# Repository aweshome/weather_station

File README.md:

# Weather station

## Internal unit (terminal)

### Heart:
	ATmega1284
	
### Peripherals:
	EG9018C - 640x480 8.4" mono lcd screen
	DS3231 - rtc
	BMP180 - pressure sensor
	nRF24L01 - wireless transceiver
	AM2302 - temperature and humidity sensor

## External unit (sensor)

### Heart:
	ATxmega128A3U - uC
	
### Peripherals:
	PMSA003 - dust sensor
	nRF24L01
	AM2302

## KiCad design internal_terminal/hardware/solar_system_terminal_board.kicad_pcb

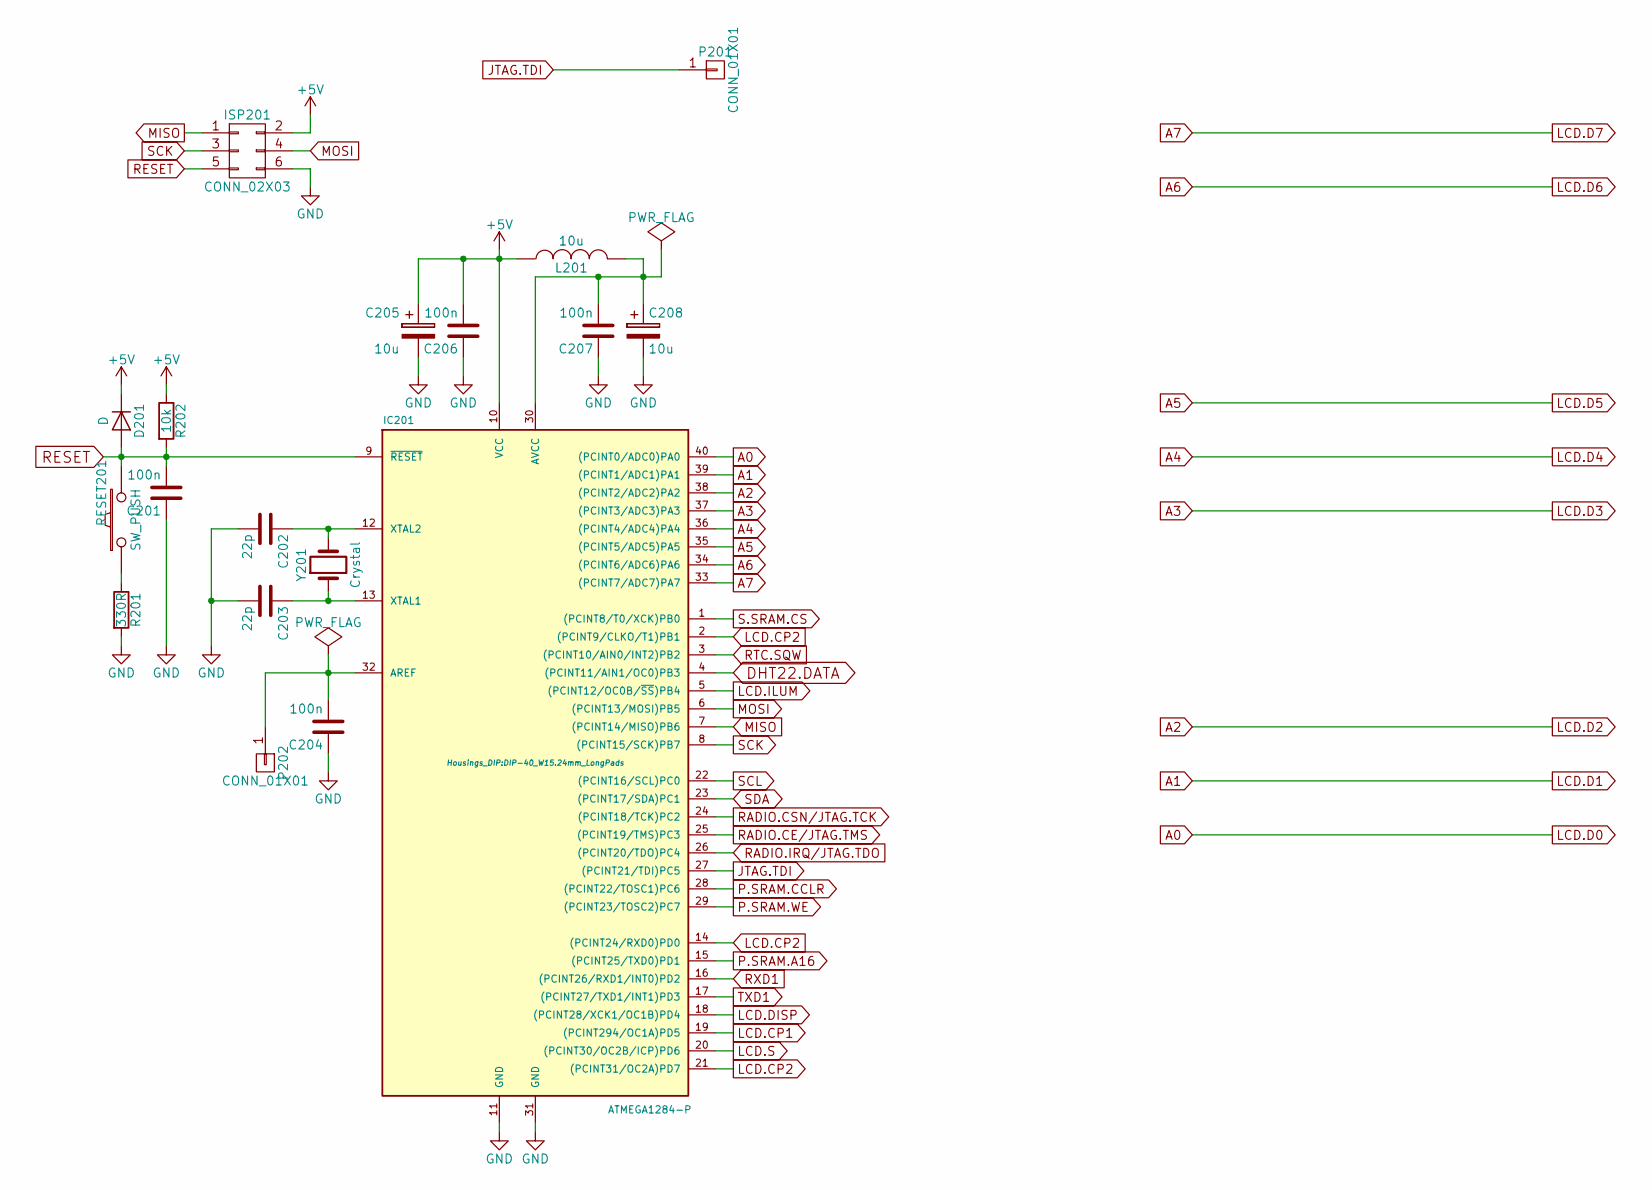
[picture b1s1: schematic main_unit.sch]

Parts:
C201, C204, C206, C207: 100n; C_1206_HandSoldering
C202, C203: 22p; C_1206_HandSoldering
C205, C208: 10u; TantalC_SizeB_EIA-3528_HandSoldering
D201: D; Diode-MiniMELF_Handsoldering
IC201: ATMEGA1284-P; DIP-40_W15.24mm_LongPads
ISP201: CONN_02X03; Pin_Header_Angled_2x03
L201: 10u; Neosid_Inductor_SM-NE45_SMD1812
P201, P202: CONN_01X01; Pin_Header_Straight_1x01
R201: 330R; R_1206_HandSoldering
R202: 10k; R_1206_HandSoldering
RESET201: SW_PUSH; SW_Tactile_SPST_Angled
Y201: Crystal; Crystal_HC49-U_Horizontal_Typ1

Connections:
+5V: C205.1, C206.2, D201.1 (K), IC201.10 (VCC), ISP201.2, L201.1, R202.1; also elsewhere on the board
A0: IC201.40 ((PCINT0/ADC0)PA0); also elsewhere on the board
A1: IC201.39 ((PCINT1/ADC1)PA1); also elsewhere on the board
A2: IC201.38 ((PCINT2/ADC2)PA2); also elsewhere on the board
A3: IC201.37 ((PCINT3/ADC3)PA3); also elsewhere on the board
A4: IC201.36 ((PCINT4/ADC4)PA4); also elsewhere on the board
A5: IC201.35 ((PCINT5/ADC5)PA5); also elsewhere on the board
A6: IC201.34 ((PCINT6/ADC6)PA6); also elsewhere on the board
A7: IC201.33 ((PCINT7/ADC7)PA7); also elsewhere on the board
DHT22.DATA: IC201.4 ((PCINT11/AIN1/OC0)PB3); also elsewhere on the board
GND: C201.1, C202.2, C203.2, C204.1, C205.2, C206.1, C207.1, C208.2, IC201.11 (GND), IC201.31 (GND), ISP201.6, R201.2; also elsewhere on the board
JTAG.TDI: IC201.27 ((PCINT21/TDI)PC5), P201.1
LCD.CP1: IC201.19 ((PCINT294/OC1A)PD5); also elsewhere on the board
LCD.CP2: IC201.2 ((PCINT9/CLKO/T1)PB1), IC201.14 ((PCINT24/RXD0)PD0), IC201.21 ((PCINT31/OC2A)PD7); also elsewhere on the board
LCD.DISP: IC201.18 ((PCINT28/XCK1/OC1B)PD4); also elsewhere on the board
LCD.ILUM: IC201.5 ((PCINT12/OC0B/~SS~)PB4); also elsewhere on the board
LCD.S: IC201.20 ((PCINT30/OC2B/ICP)PD6); also elsewhere on the board
MISO: IC201.7 ((PCINT14/MISO)PB6), ISP201.1; also elsewhere on the board
MOSI: IC201.6 ((PCINT13/MOSI)PB5), ISP201.4; also elsewhere on the board
unnamed: C202.1, IC201.12 (XTAL2), Y201.2
unnamed: C203.1, IC201.13 (XTAL1), Y201.1
unnamed: C204.2, IC201.32 (AREF), P202.1
unnamed: C207.2, C208.1, IC201.30 (AVCC), L201.2
unnamed: R201.1, RESET201.1
P.SRAM.A16: IC201.15 ((PCINT25/TXD0)PD1); also elsewhere on the board
P.SRAM.CCLR: IC201.28 ((PCINT22/TOSC1)PC6); also elsewhere on the board
P.SRAM.WE: IC201.29 ((PCINT23/TOSC2)PC7); also elsewhere on the board
RADIO.CE/JTAG.TMS: IC201.25 ((PCINT19/TMS)PC3); also elsewhere on the board
RADIO.CSN/JTAG.TCK: IC201.24 ((PCINT18/TCK)PC2); also elsewhere on the board
RADIO.IRQ/JTAG.TDO: IC201.26 ((PCINT20/TDO)PC4); also elsewhere on the board
RESET: C201.2, D201.2 (A), IC201.9 (~RESET), ISP201.5, R202.2, RESET201.2
RTC.SQW: IC201.3 ((PCINT10/AIN0/INT2)PB2); also elsewhere on the board
RXD1: IC201.16 ((PCINT26/RXD1/INT0)PD2); also elsewhere on the board
S.SRAM.CS: IC201.1 ((PCINT8/T0/XCK)PB0); also elsewhere on the board
SCK: IC201.8 ((PCINT15/SCK)PB7), ISP201.3; also elsewhere on the board
SCL: IC201.22 ((PCINT16/SCL)PC0); also elsewhere on the board
SDA: IC201.23 ((PCINT17/SDA)PC1); also elsewhere on the board
TXD1: IC201.17 ((PCINT27/TXD1/INT1)PD3); also elsewhere on the board

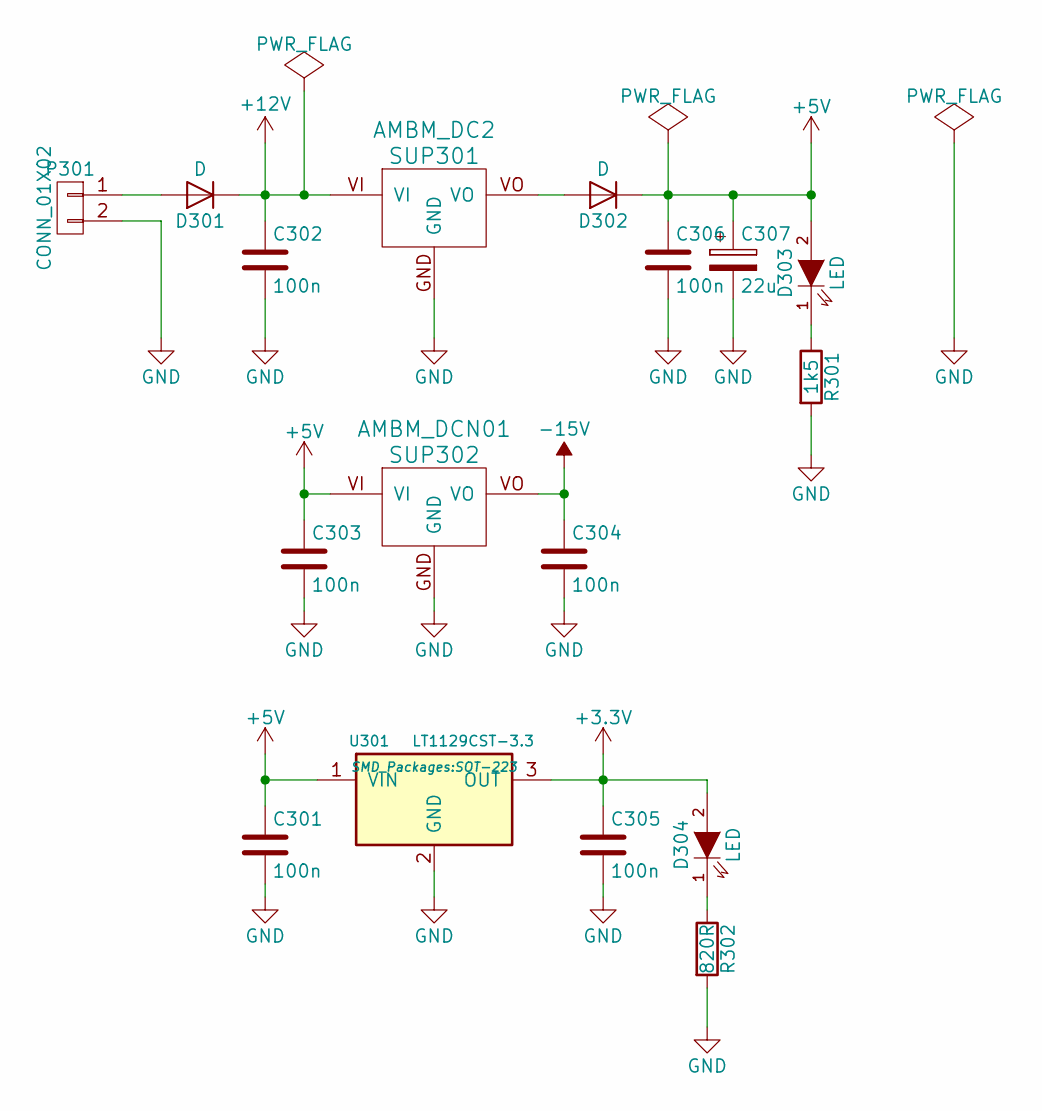
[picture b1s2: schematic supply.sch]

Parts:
C301, C302, C303, C304, C305, C306: 100n; C_1206_HandSoldering
C307: 22u; TantalC_SizeB_EIA-3528_HandSoldering
D301, D302: D; Diode-MiniMELF_Handsoldering
D303, D304: LED; LED-1206
P301: CONN_01X02; AK300-2
R301: 1k5; R_1206_HandSoldering
R302: 820R; R_1206_HandSoldering
SUP301: AMBM_DC2; DC2_Socket_H
SUP302: AMBM_DCN01; DC2_Socket_H
U301: LT1129CST-3.3; SOT-223

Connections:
+3V3: C305.1, D304.2 (A), U301.3 (OUT); also elsewhere on the board
+5V: C301.1, C303.1, C306.1, C307.1, D302.1 (K), D303.2 (A), SUP302.VI, U301.1 (VIN); also elsewhere on the board
+12V: C302.1, D301.1 (K), SUP301.VI; also elsewhere on the board
-15V: C304.1, SUP302.VO; also elsewhere on the board
GND: C301.2, C302.2, C303.2, C304.2, C305.2, C306.2, C307.2, P301.2, R301.2, R302.2, SUP301.GND, SUP302.GND, U301.2 (GND); also elsewhere on the board
unnamed: D301.2 (A), P301.1
unnamed: D302.2 (A), SUP301.VO
unnamed: D303.1 (K), R301.1
unnamed: D304.1 (K), R302.1

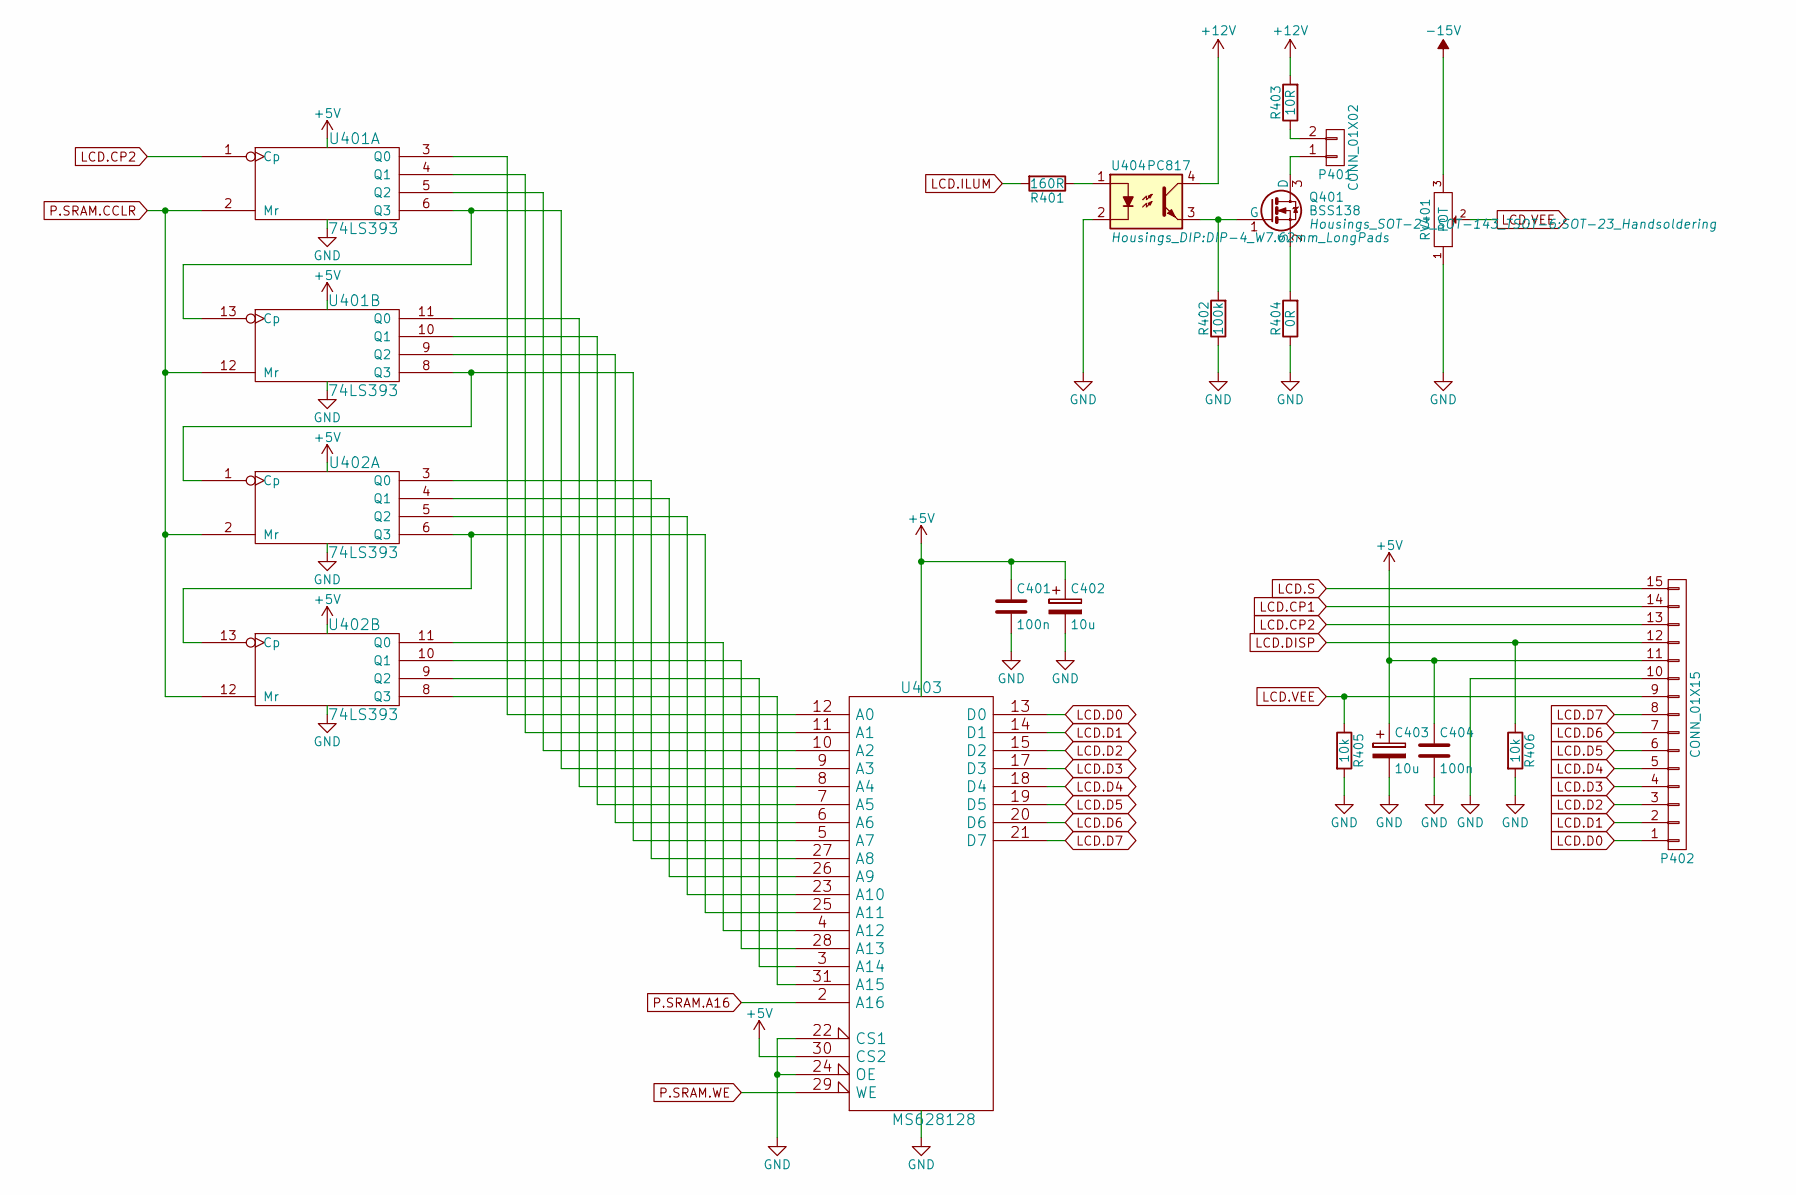
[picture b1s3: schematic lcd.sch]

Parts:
C401, C404: 100n; C_1206_HandSoldering
C402, C403: 10u; TantalC_SizeB_EIA-3528_HandSoldering
P401: CONN_01X02; Pin_Header_Angled_1x02
P402: CONN_01X15; Socket_Strip_Straight_1x15
Q401: BSS138; SOT-23_Handsoldering
R401: 160R; R_1206_HandSoldering
R402: 100k; R_1206_HandSoldering
R403: 10R; R_1206_HandSoldering
R404: 0R; R_1206_HandSoldering
R405, R406: 10k; R_1206_HandSoldering
RV401: POT; Potentiometer_Bourns_3296W_3-8Zoll_Inline_ScrewUp
U401, U402: 74LS393; DIP-14_W7.62mm_LongPads
U403: MS628128; DIP-32_W15.24mm_LongPads
U404: PC817; DIP-4_W7.62mm_LongPads

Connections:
+5V: C401.1, C402.1, C403.1, C404.1, P402.11, U401.14 (VCC), U402.14 (VCC), U403.30 (CS2), U403.32 (VCC); also elsewhere on the board
+12V: R403.2, U404.4; also elsewhere on the board
-15V: RV401.3; also elsewhere on the board
A0: P402.1, U403.13 (D0); also elsewhere on the board
A1: P402.2, U403.14 (D1); also elsewhere on the board
A2: P402.3, U403.15 (D2); also elsewhere on the board
A3: P402.4, U403.17 (D3); also elsewhere on the board
A4: P402.5, U403.18 (D4); also elsewhere on the board
A5: P402.6, U403.19 (D5); also elsewhere on the board
A6: P402.7, U403.20 (D6); also elsewhere on the board
A7: P402.8, U403.21 (D7); also elsewhere on the board
GND: C401.2, C402.2, C403.2, C404.2, P402.10, R402.1, R404.1, R405.2, R406.2, RV401.1, U401.7 (GND), U402.7 (GND), U403.16 (GND), U403.22 (CS1), U403.24 (OE), U404.2; also elsewhere on the board
LCD.CP1: P402.14; also elsewhere on the board
LCD.CP2: P402.13, U401.1 (Cp); also elsewhere on the board
LCD.DISP: P402.12, R406.1; also elsewhere on the board
LCD.ILUM: R401.2; also elsewhere on the board
LCD.S: P402.15; also elsewhere on the board
LCD.VEE: P402.9, R405.1, RV401.2
unnamed: P401.1, Q401.3 (D)
unnamed: P401.2, R403.1
unnamed: Q401.1 (G), R402.2, U404.3
unnamed: Q401.2 (S), R404.2
unnamed: R401.1, U404.1
unnamed: U401.3 (Q0), U403.12 (A0)
unnamed: U401.4 (Q1), U403.11 (A1)
unnamed: U401.5 (Q2), U403.10 (A2)
unnamed: U401.8 (Q3), U402.1 (Cp), U403.5 (A7)
unnamed: U401.9 (Q2), U403.6 (A6)
unnamed: U401.10 (Q1), U403.7 (A5)
unnamed: U401.11 (Q0), U403.8 (A4)
unnamed: U401.6 (Q3), U401.13 (Cp), U403.9 (A3)
unnamed: U402.3 (Q0), U403.27 (A8)
unnamed: U402.4 (Q1), U403.26 (A9)
unnamed: U402.5 (Q2), U403.23 (A10)
unnamed: U402.8 (Q3), U403.31 (A15)
unnamed: U402.9 (Q2), U403.3 (A14)
unnamed: U402.10 (Q1), U403.28 (A13)
unnamed: U402.11 (Q0), U403.4 (A12)
unnamed: U402.6 (Q3), U402.13 (Cp), U403.25 (A11)
P.SRAM.A16: U403.2 (A16); also elsewhere on the board
P.SRAM.CCLR: U401.2 (Mr), U401.12 (Mr), U402.2 (Mr), U402.12 (Mr); also elsewhere on the board
P.SRAM.WE: U403.29 (WE); also elsewhere on the board

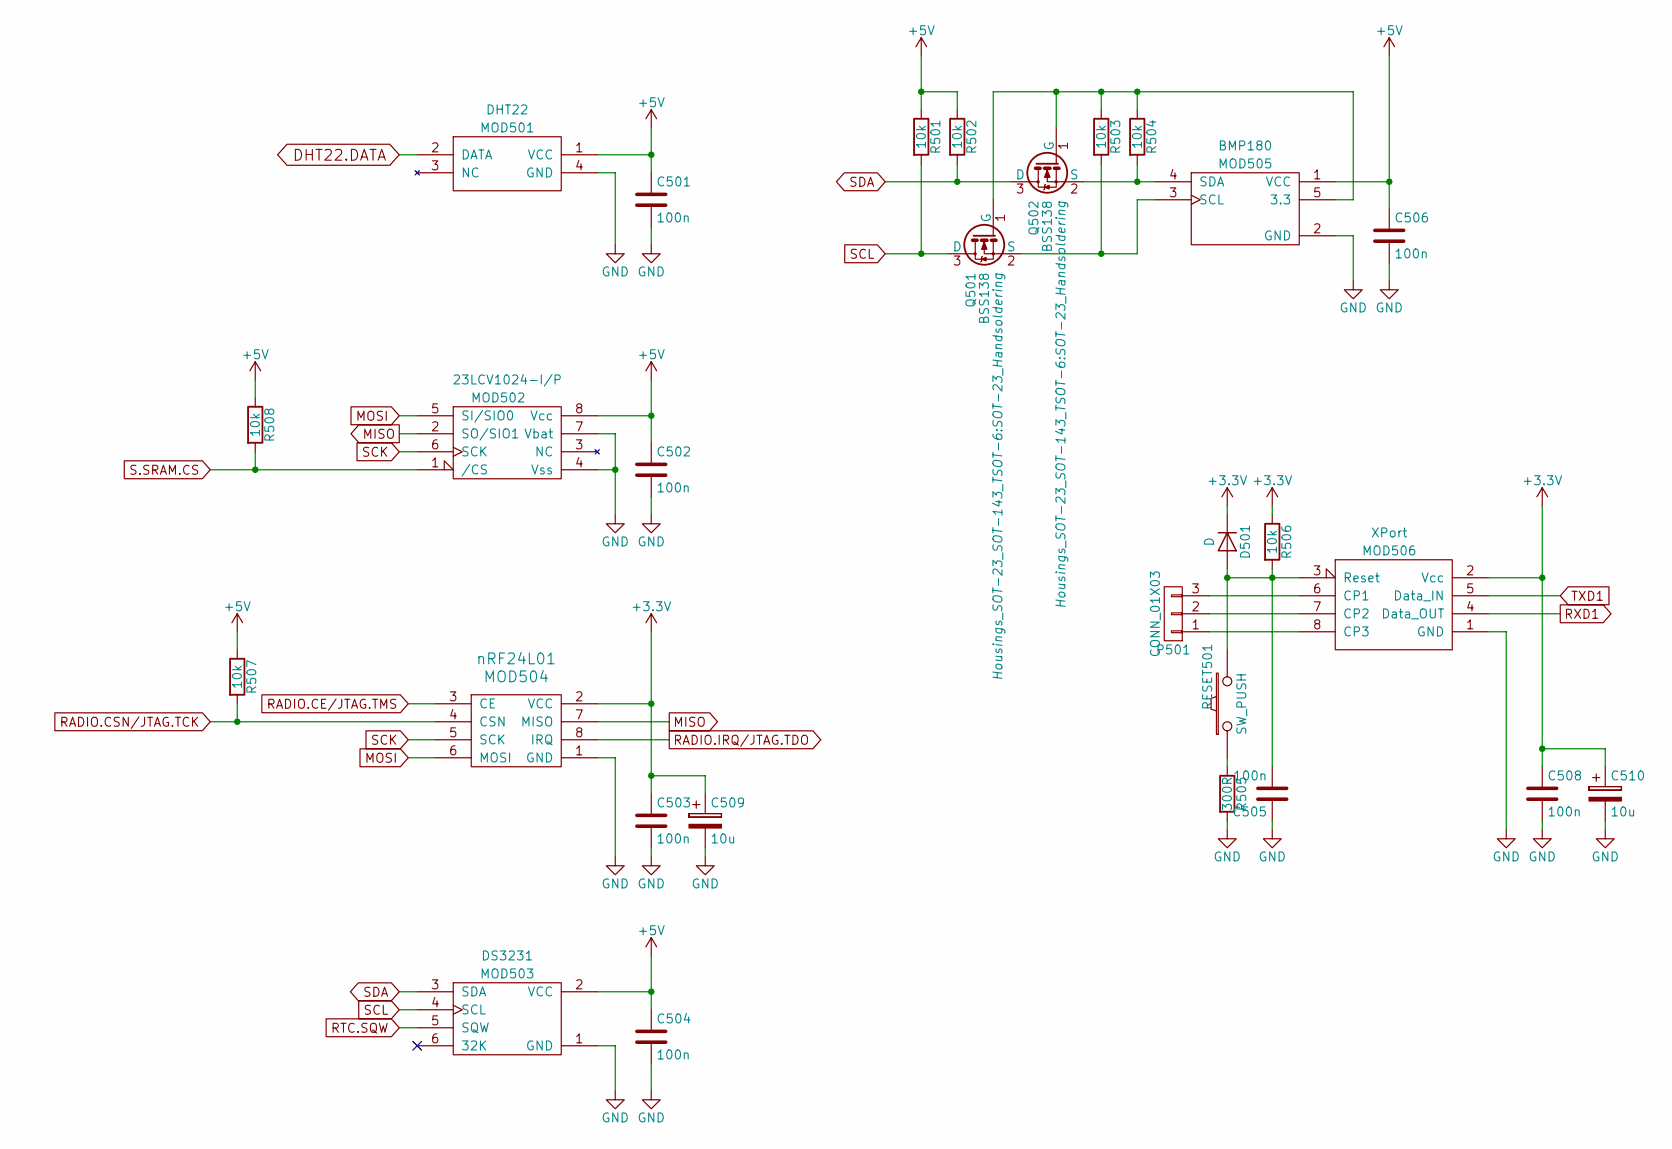
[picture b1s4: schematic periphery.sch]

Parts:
C501, C502, C503, C504, C505, C506, C508: 100n; C_1206_HandSoldering
C509, C510: 10u; TantalC_SizeB_EIA-3528_HandSoldering
D501: D; Diode-MiniMELF_Handsoldering
MOD501: DHT22; AM2302_Socket_H
MOD502: 23LCV1024-I/P; DIP-8_W7.62mm_LongPads
MOD503: DS3231; DS3231_Socket_H
MOD504: nRF24L01
MOD505: BMP180; BMP180_Socket_H
MOD506: XPort
P501: CONN_01X03; Pin_Header_Straight_1x03
Q501, Q502: BSS138; SOT-23_Handsoldering
R501, R502, R503, R504, R506, R507, R508: 10k; R_1206_HandSoldering
R505: 300R; R_1206_HandSoldering
RESET501: SW_PUSH; SW_Tactile_SPST_Angled

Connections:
+3V3: C503.1, C508.1, C509.1, C510.1, D501.1 (K), MOD504.2 (VCC), MOD506.2 (Vcc), R506.1; also elsewhere on the board
+5V: C501.1, C502.1, C504.1, C506.1, MOD501.1 (VCC), MOD502.8 (Vcc), MOD503.2 (VCC), MOD505.1 (VCC), R501.1, R502.1, R507.1, R508.1; also elsewhere on the board
DHT22.DATA: MOD501.2 (DATA); also elsewhere on the board
GND: C501.2, C502.2, C503.2, C504.2, C505.1, C506.2, C508.2, C509.2, C510.2, MOD501.4 (GND), MOD502.4 (Vss), MOD502.7 (Vbat), MOD503.1 (GND), MOD504.1 (GND), MOD505.2 (GND), MOD506.1 (GND), R505.2; also elsewhere on the board
MISO: MOD502.2 (SO/SIO1), MOD504.7 (MISO); also elsewhere on the board
MOSI: MOD502.5 (SI/SIO0), MOD504.6 (MOSI); also elsewhere on the board
unnamed: C505.2, D501.2 (A), MOD506.3 (Reset), R506.2, RESET501.2
unnamed: MOD505.3 (SCL), Q501.2 (S), R503.2
unnamed: MOD505.4 (SDA), Q502.2 (S), R504.2
unnamed: MOD505.5 (3.3), Q501.1 (G), Q502.1 (G), R503.1, R504.1
unnamed: MOD506.6 (CP1), P501.3
unnamed: MOD506.7 (CP2), P501.2
unnamed: MOD506.8 (CP3), P501.1
unnamed: R505.1, RESET501.1
RADIO.CE/JTAG.TMS: MOD504.3 (CE); also elsewhere on the board
RADIO.CSN/JTAG.TCK: MOD504.4 (CSN), R507.2; also elsewhere on the board
RADIO.IRQ/JTAG.TDO: MOD504.8 (IRQ); also elsewhere on the board
RTC.SQW: MOD503.5 (SQW); also elsewhere on the board
RXD1: MOD506.4 (Data_OUT); also elsewhere on the board
S.SRAM.CS: MOD502.1 (/CS), R508.2; also elsewhere on the board
SCK: MOD502.6 (SCK), MOD504.5 (SCK); also elsewhere on the board
SCL: MOD503.4 (SCL), Q501.3 (D), R501.2; also elsewhere on the board
SDA: MOD503.3 (SDA), Q502.3 (D), R502.2; also elsewhere on the board
TXD1: MOD506.5 (Data_IN); also elsewhere on the board

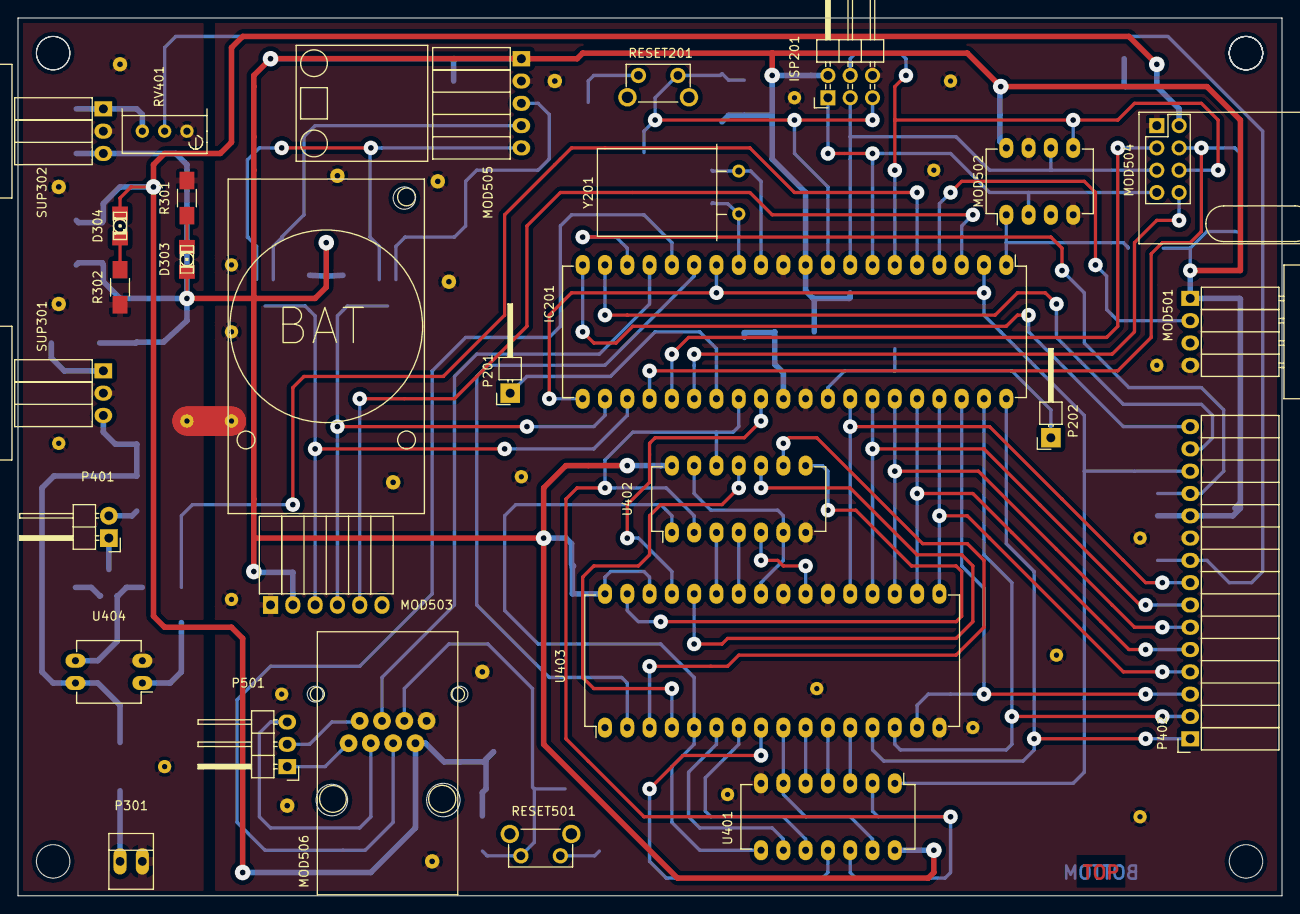
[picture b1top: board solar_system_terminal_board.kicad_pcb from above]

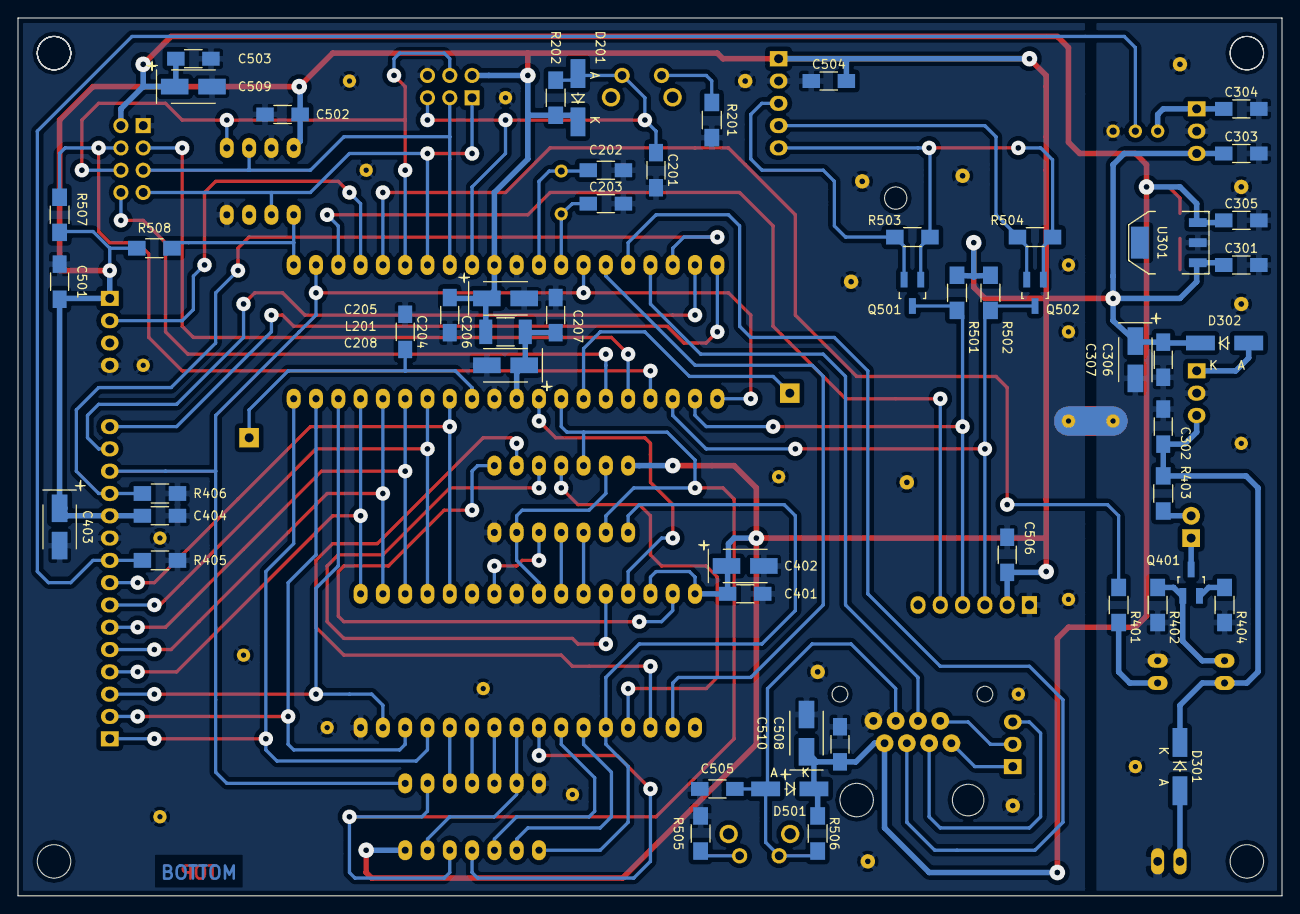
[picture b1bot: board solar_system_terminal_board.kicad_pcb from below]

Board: 2 copper layers, 144.0 x 100.0 mm, 81 parts (53 on the bottom side), 75 nets.

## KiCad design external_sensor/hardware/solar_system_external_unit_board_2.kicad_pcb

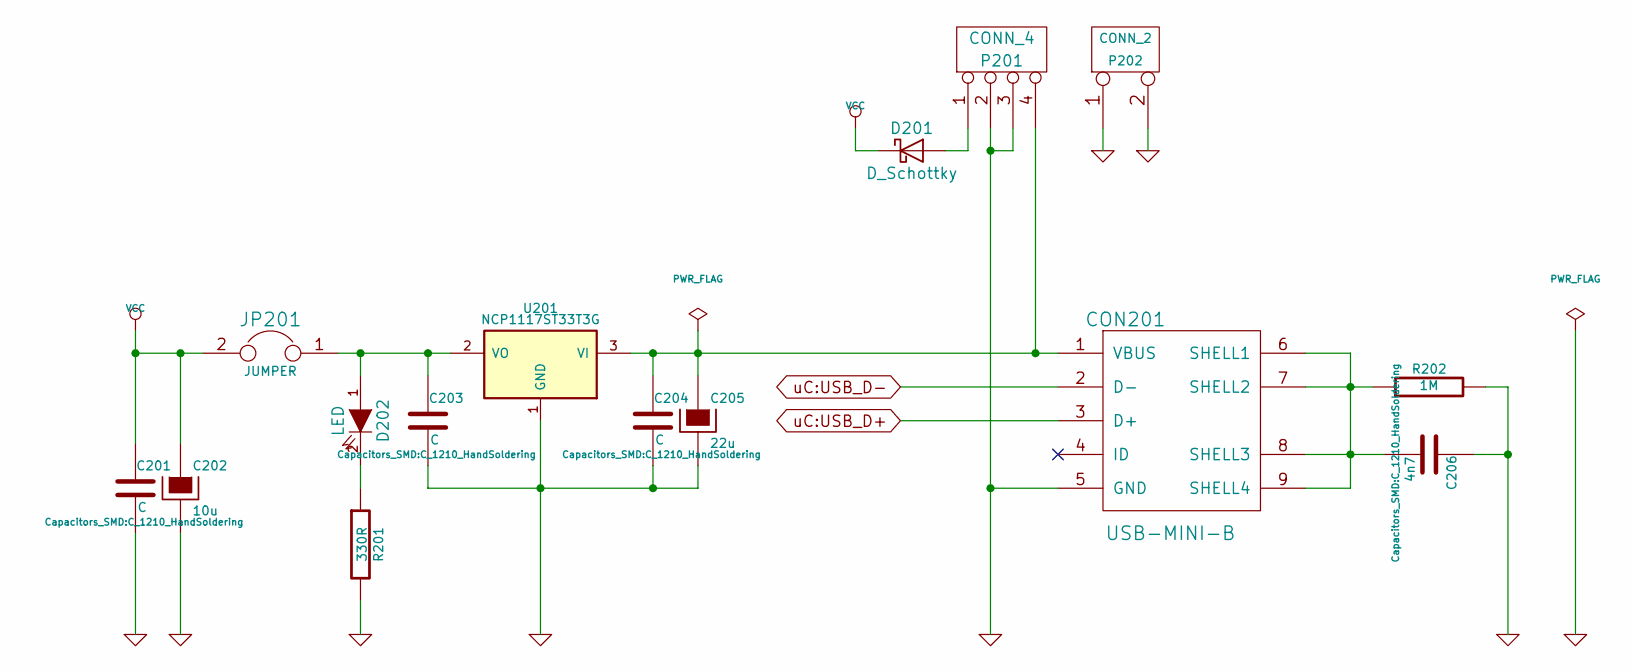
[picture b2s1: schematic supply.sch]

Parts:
C201, C203, C204: C; C_1210_HandSoldering
C202: 10u; TantalC_SizeB_EIA-3528_HandSoldering
C205: 22u; TantalC_SizeB_EIA-3528_HandSoldering
C206: 4n7; C_1210_HandSoldering
CON201: USB-MINI-B; USB_Mini-B_mod
D201: D_Schottky; MiniMELF_Handsoldering
D202: LED; LED_1206
JP201: JUMPER; Pin_Header_Straight_1x02
P201: CONN_4; pt_1,5-4-3,5-h
P202: CONN_2; pt_1,5-2-3,5-h
R201: 330R; R_1206_HandSoldering
R202: 1M; R_1206_HandSoldering
U201: NCP1117ST33T3G; SOT-223

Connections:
GND: C201.2, C202.2, C203.2, C204.2, C205.2, C206.1, CON201.5 (GND), P201.2, P201.3, P202.1, P202.2 (PM), R201.2, R202.2, U201.1 (GND); also elsewhere on the board
unnamed: C203.1, D202.1 (A), JP201.1, U201.2 (VO)
unnamed: C204.1, C205.1, CON201.1 (VBUS), P201.4, U201.3 (VI)
unnamed: C206.2, CON201.6 (SHELL1), CON201.7 (SHELL2), CON201.8 (SHELL3), CON201.9 (SHELL4), R202.1
unnamed: D201.2 (A), P201.1
unnamed: D202.2 (K), R201.1
VCC: C201.1, C202.1, D201.1 (K), JP201.2; also elsewhere on the board
uC:USB_D+: CON201.3 (D+); also elsewhere on the board
uC:USB_D-: CON201.2 (D-); also elsewhere on the board

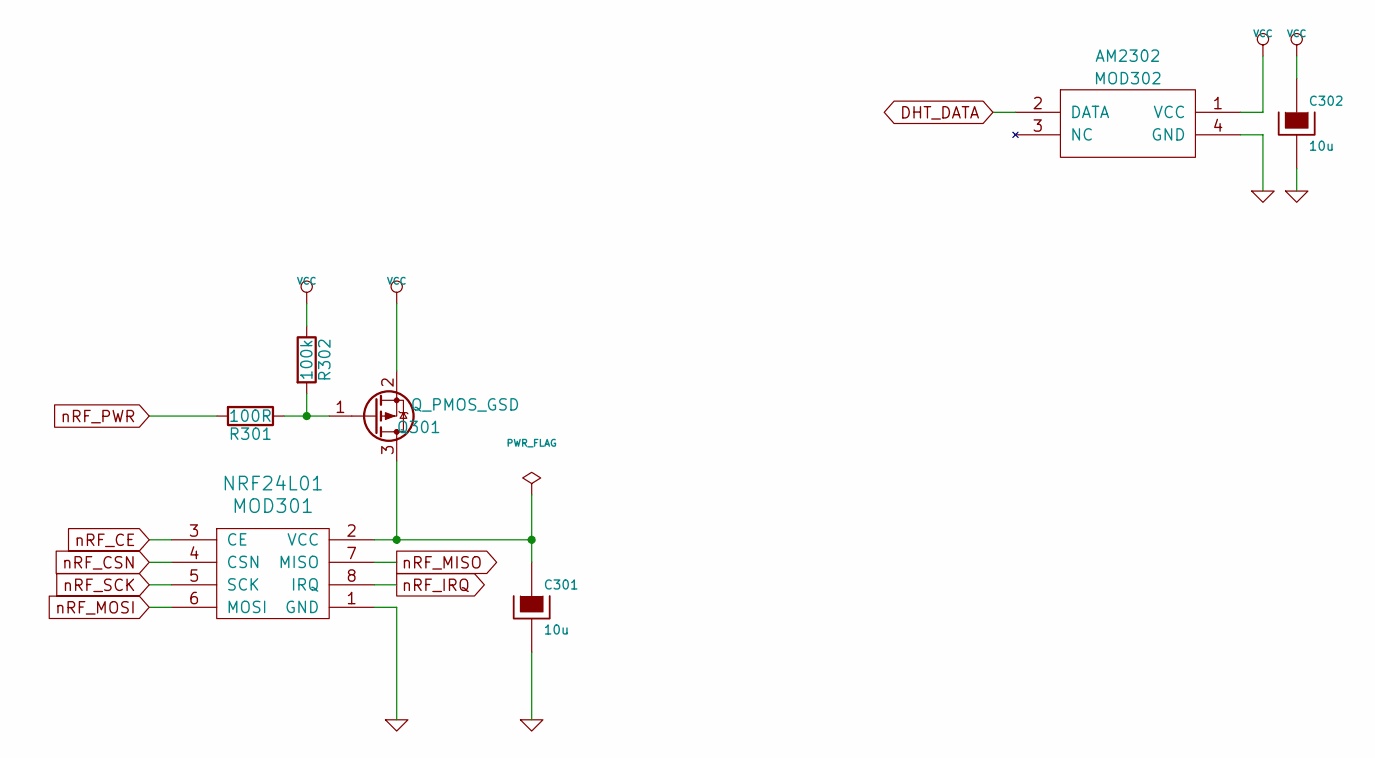
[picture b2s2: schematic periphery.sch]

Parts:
C301, C302: 10u; TantalC_SizeB_EIA-3528_HandSoldering
MOD301: NRF24L01; nRF24L01
MOD302: AM2302; AM2302_Naked_H
Q301: Q_PMOS_GSD; SOT-23_Handsoldering
R301: 100R; R_1206_HandSoldering
R302: 100k; R_1206_HandSoldering

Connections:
DHT_DATA: MOD302.2 (DATA); also elsewhere on the board
GND: C301.2, C302.2, MOD301.1 (GND), MOD302.4 (GND); also elsewhere on the board
unnamed: C301.1, MOD301.2 (VCC), Q301.3 (D)
unnamed: Q301.1 (G), R301.1, R302.2
VCC: C302.1, MOD302.1 (VCC), Q301.2 (S), R302.1; also elsewhere on the board
nRF_CE: MOD301.3 (CE); also elsewhere on the board
nRF_CSN: MOD301.4 (CSN); also elsewhere on the board
nRF_IRQ: MOD301.8 (IRQ); also elsewhere on the board
nRF_MISO: MOD301.7 (MISO); also elsewhere on the board
nRF_MOSI: MOD301.6 (MOSI); also elsewhere on the board
nRF_PWR: R301.2; also elsewhere on the board
nRF_SCK: MOD301.5 (SCK); also elsewhere on the board
